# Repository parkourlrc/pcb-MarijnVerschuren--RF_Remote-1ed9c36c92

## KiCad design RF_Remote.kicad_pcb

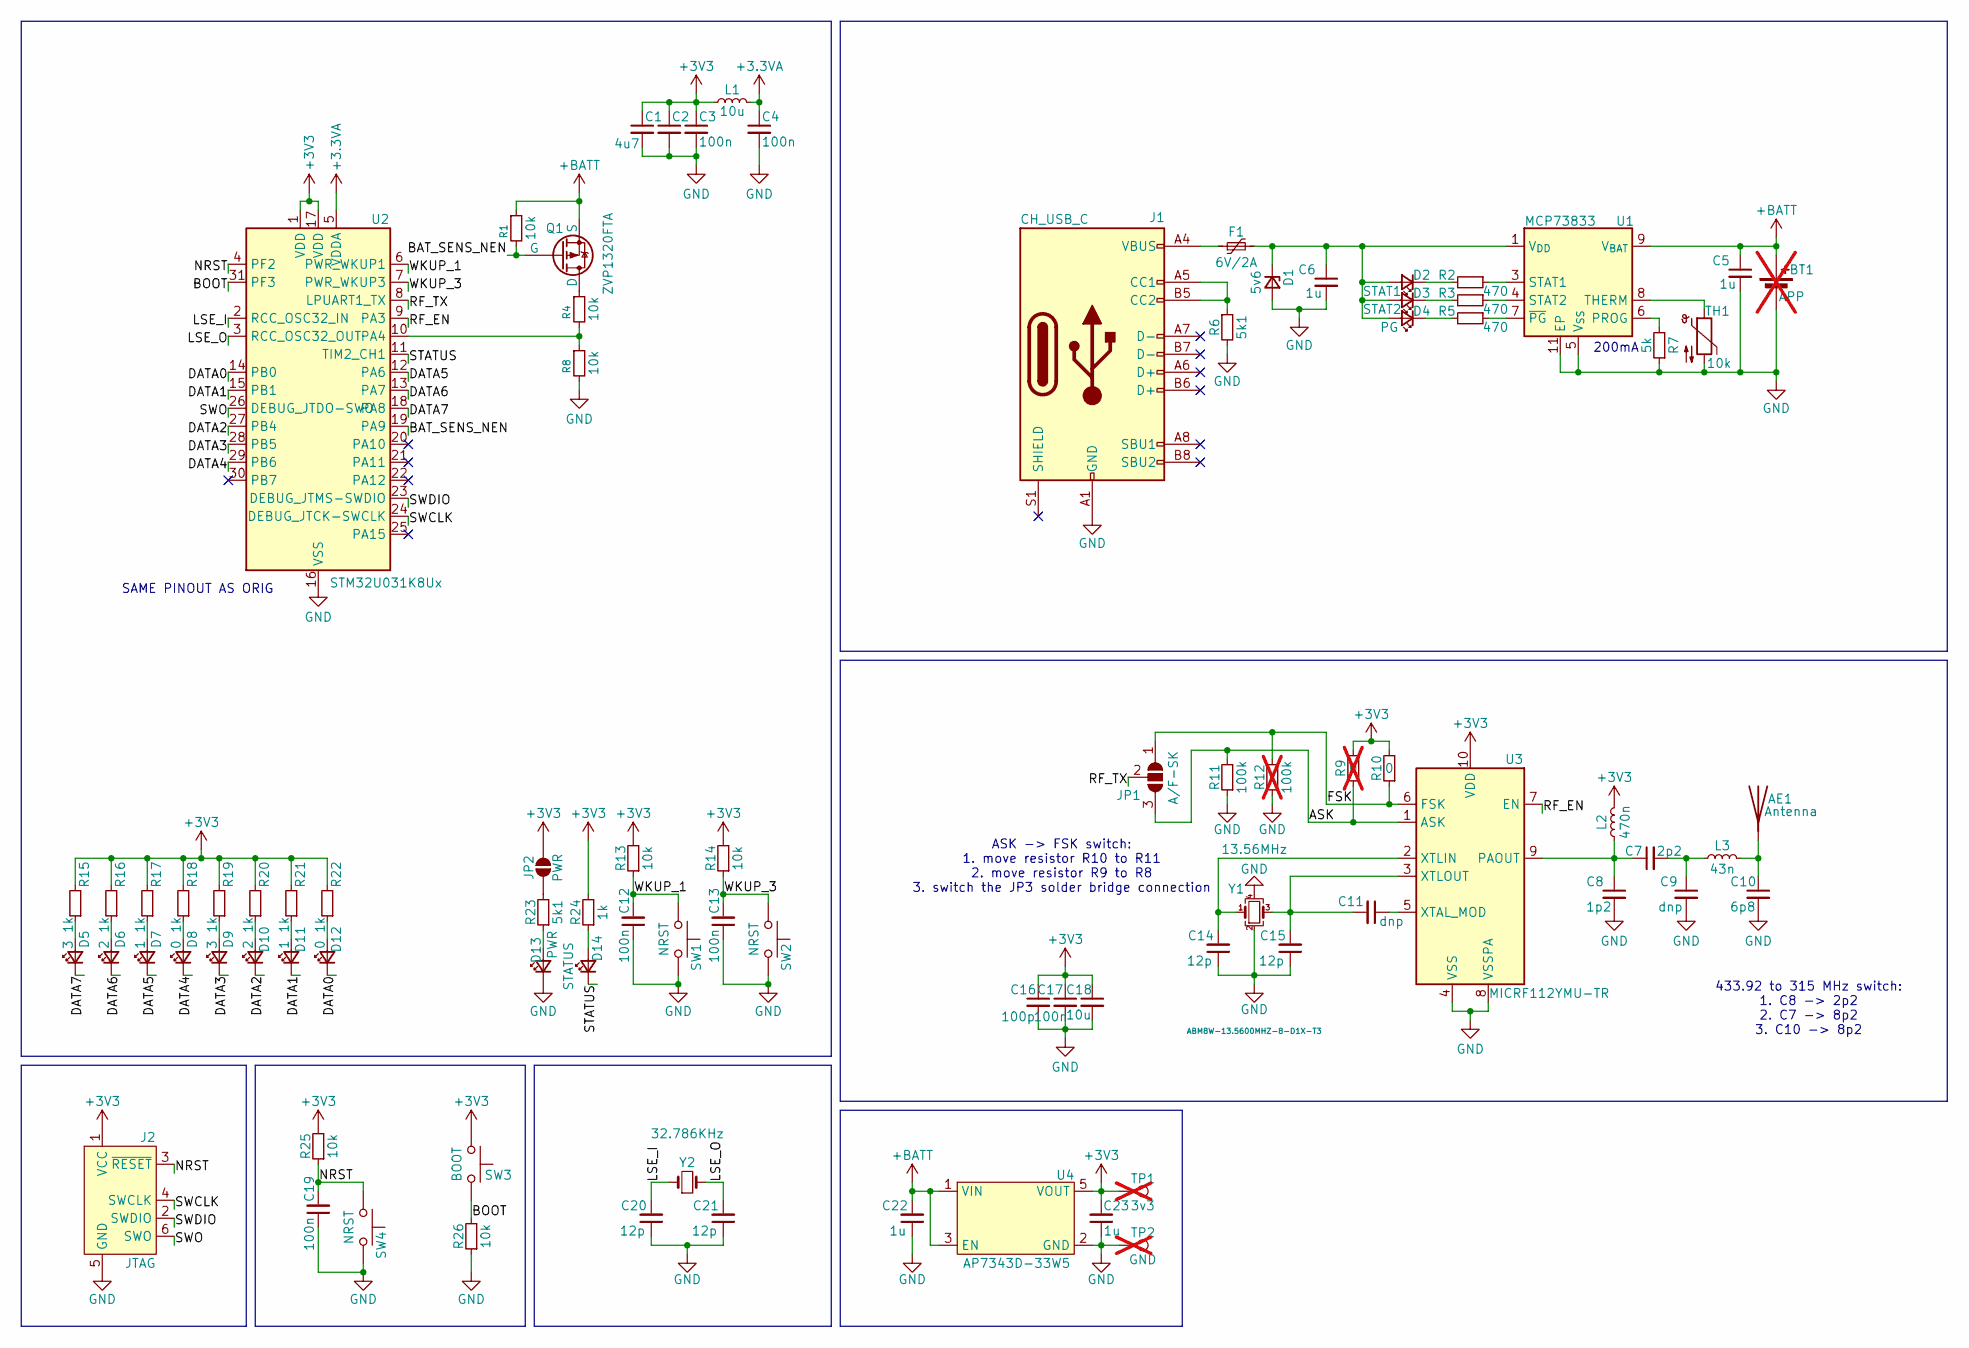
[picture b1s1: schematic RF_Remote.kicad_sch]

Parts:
AE1: Antenna; TestPoint_THTPad_D1.0mm_Drill0.5mm
BT1: APP; PinHeader_1x02_P2.54mm_Vertical; not fitted
C1: 4u7; C_0603_1608Metric
C2, C3, C4, C12, C13, C17, C19: 100n; C_0603_1608Metric
C5, C6: 1u; C_0603_1608Metric; mouser 963-MLAST168SB7105KT
C7: 2p2; C_0603_1608Metric
C8: 1p2; C_0603_1608Metric
C9, C11: dnp; C_0603_1608Metric
C10: 6p8; C_0603_1608Metric
C14, C15, C20, C21: 12p; C_0603_1608Metric
C16: 100p; C_0603_1608Metric
C18: 10u; C_0603_1608Metric
C22, C23: 1u; C_0603_1608Metric
D1: 5v6; D_SOD-123; mouser 78-BZT52C5V6-E3-08
D2: STAT1; LED_0603_1608Metric; mouser 710-150060AS75000
D3: STAT2; LED_0603_1608Metric; mouser 710-150060AS75000
D4: PG; LED_0603_1608Metric; mouser 710-150060RS75000
D5, D9: 3; LED_0603_1608Metric; mouser 710-150060AS75000
D6, D10: 2; LED_0603_1608Metric; mouser 710-150060AS75000
D7, D11: 1; LED_0603_1608Metric; mouser 710-150060AS75000
D8, D12: 0; LED_0603_1608Metric; mouser 710-150060AS75000
D13: PWR; LED_0603_1608Metric; mouser 710-150060AS75000
D14: STATUS; LED_0603_1608Metric; mouser 710-150060AS75000
F1: 6V/2A; Fuse_1206_3216Metric; mouser 504-PTS18126V260
J1: CH_USB_C; USB_C_Receptacle_HCTL_HC-TYPE-C-16P-01A
J2: JTAG; Tag-Connect_TC2030-IDC-FP_2x03_P1.27mm_Vertical
JP1: A/F-SK; SolderJumper-3_P2.0mm_Open_TrianglePad1.0x1.5mm_NumberLabels
JP2: PWR; SolderJumper-2_P1.3mm_Open_TrianglePad1.0x1.5mm
L1: 10u; L_0805_2012Metric
L2: 470n; L_0805_2012Metric
L3: 43n; L_0805_2012Metric
Q1: ZVP1320FTA; SOT-323; mouser 522-ZVP1320FTA
R1, R4, R8, R13, R14, R25, R26: 10k; R_0603_1608Metric
R2, R3, R5: 470; R_0603_1608Metric; LCSC C23186
R6: 5k1; R_0603_1608Metric; LCSC C23186
R7: 5k; R_0603_1608Metric; LCSC C23186
R9: 0; R_0603_1608Metric; not fitted
R10: 0; R_0603_1608Metric
R11: 100k; R_0603_1608Metric
R12: 100k; R_0603_1608Metric; not fitted
R15, R16, R17, R18, R19, R20, R21, R22, R24: 1k; R_0603_1608Metric
R23: 5k1; R_0603_1608Metric
SW1, SW2, SW4: NRST; SW_SPST_PTS810; LCSC C2681476
SW3: BOOT; SW_SPST_PTS810; LCSC C2681476
TH1: 10k; R_0603_1608Metric; mouser 667-ERT-J1VR103J
TP1: 3v3; TestPoint_Pad_D1.5mm; not fitted
TP2: GND; TestPoint_Pad_D1.5mm; not fitted
U1: MCP73833; DFN-10-1EP_3x3mm_P0.5mm_EP1.58x2.35mm; mouser 579-MCP73833T-AMI/MF
U2: STM32U031K8Ux; QFN-32-1EP_5x5mm_P0.5mm_EP3.45x3.45mm
U3: MICRF112YMU-TR; DFN-10-1EP_2.6x2.6mm_P0.5mm_EP1.3x2.2mm
U4: AP7343D-33W5; SOT-25
Y1: 13.56MHz; Crystal_SMD_3225-4Pin_3.2x2.5mm
Y2: 32.786KHz; Crystal_SMD_3215-2Pin_3.2x1.5mm

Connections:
+3.3VA: C4.1, L1.2, U2.5 (VDDA)
+3V3: C1.1, C2.1, C3.1, C16.1, C17.1, C18.1, C23.2, J2.1 (VCC), JP2.2 (B), L1.1, L2.2, R9.2, R10.2, R13.2, R14.2, R15.2, R16.2, R17.2, R18.2, R19.2, R20.2, R21.2, R22.2, R24.2, R25.2, SW3.1, TP1.1, U2.1 (VDD), U2.17 (VDD), U3.10 (VDD), U4.5 (VOUT)
+BATT: BT1.1 (+), C5.1, C22.2, Q1.3 (S), R1.1, U1.9 (V_{BAT}), U1.10 (V_{BAT}), U4.1 (VIN), U4.3 (EN)
/ASK: JP1.3 (B), R9.1, R11.2, U3.1 (ASK)
/BAT_SENS_NEN: Q1.2 (G), R1.2, U2.19 (PA9)
/BOOT: R26.2, SW3.2, U2.31 (PF3)
/DATA0: D12.1 (K), U2.14 (PB0)
/DATA1: D11.1 (K), U2.15 (PB1)
/DATA2: D10.1 (K), U2.27 (PB4)
/DATA3: D9.1 (K), U2.28 (PB5)
/DATA4: D8.1 (K), U2.29 (PB6)
/DATA5: D7.1 (K), U2.12 (PA6)
/DATA6: D6.1 (K), U2.13 (PA7)
/DATA7: D5.1 (K), U2.18 (PA8)
/FSK: JP1.1 (A), R10.1, R12.2, U3.6 (FSK)
/LSE_I: C20.2, U2.2 (RCC_OSC32_IN), Y2.1
/LSE_O: C21.2, U2.3 (RCC_OSC32_OUT), Y2.2
/NRST: C19.2, J2.3 (~RESET), R25.1, SW4.1, U2.4 (PF2)
/RF_EN: U2.9 (PA3), U3.7 (EN)
/RF_TX: JP1.2 (C), U2.8 (LPUART1_TX)
/STATUS: D14.1 (K), U2.11 (TIM2_CH1)
/SWCLK: J2.4 (SWCLK), U2.24 (DEBUG_JTCK-SWCLK)
/SWDIO: J2.2 (SWDIO), U2.23 (DEBUG_JTMS-SWDIO)
/SWO: J2.6 (SWO), U2.26 (DEBUG_JTDO-SWO)
/WKUP_1: C12.2, R13.1, SW1.1, U2.6 (PWR_WKUP1)
/WKUP_3: C13.2, R14.1, SW2.1, U2.7 (PWR_WKUP3)
GND: BT1.2 (-), C1.2, C2.2, C3.2, C4.2, C5.2, C6.2, C8.2, C9.2, C10.2, C12.1, C13.1, C14.1, C15.1, C16.2, C17.2, C18.2, C19.1, C20.1, C21.1, C22.1, C23.1, D1.2 (A), D13.1 (K), J1.A1 (GND), J1.A12 (GND), J1.B1 (GND), J1.B12 (GND), J2.5 (GND), R6.2, R7.1, R8.2, R11.1, R12.1, R26.1, SW1.2, SW2.2, SW4.2, TH1.2, TP2.1, U1.5 (V_{SS}), U1.11 (EP), U2.16 (VSS), U2.32 (VSS), U2.33 (VSS), U3.4 (VSS), U3.8 (VSSPA), U4.2 (GND), Y1.2, Y1.4
unnamed: AE1.1 (A), C10.1, L3.2
unnamed: C7.2, C9.1, L3.1
unnamed: C6.1, D1.1 (K), D2.2 (A), D3.2 (A), D4.2 (A), F1.2, U1.1 (V_{DD}), U1.2 (V_{DD})
unnamed: D2.1 (K), R2.2
unnamed: D3.1 (K), R3.2
unnamed: D4.1 (K), R5.2
unnamed: D5.2 (A), R15.1
unnamed: D6.2 (A), R16.1
unnamed: D7.2 (A), R17.1
unnamed: D8.2 (A), R18.1
unnamed: D9.2 (A), R19.1
unnamed: D10.2 (A), R20.1
unnamed: D11.2 (A), R21.1
unnamed: D12.2 (A), R22.1
unnamed: D13.2 (A), R23.1
unnamed: D14.2 (A), R24.1
unnamed: F1.1, J1.A4 (VBUS), J1.A9 (VBUS), J1.B4 (VBUS), J1.B9 (VBUS)
unnamed: J1.A5 (CC1), J1.B5 (CC2), R6.1
unnamed: JP2.1 (A), R23.2
unnamed: Q1.1 (D), R4.1
unnamed: R7.2, U1.6 (PROG)
unnamed: R2.1, U1.3 (STAT1)
unnamed: R3.1, U1.4 (STAT2)
unnamed: TH1.1, U1.8 (THERM)
unnamed: R5.1, U1.7 (~PG)
unnamed: R4.2, R8.1, U2.10 (PA4)
unnamed: C7.1, C8.1, L2.1, U3.9 (PAOUT)
unnamed: C11.1, U3.5 (XTAL_MOD)
unnamed: C14.2, U3.2 (XTLIN), Y1.1
unnamed: C11.2, C15.2, U3.3 (XTLOUT), Y1.3

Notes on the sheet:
200mA
ASK -> FSK switch: 1. move resistor R10 to R11 2. move resistor R9 to R8 3. switch the JP3 solder bridge connection
433.92 to 315 MHz switch: 1. C8 -> 2p2 2. C7 -> 8p2 3. C10 -> 8p2
SAME PINOUT AS ORIG

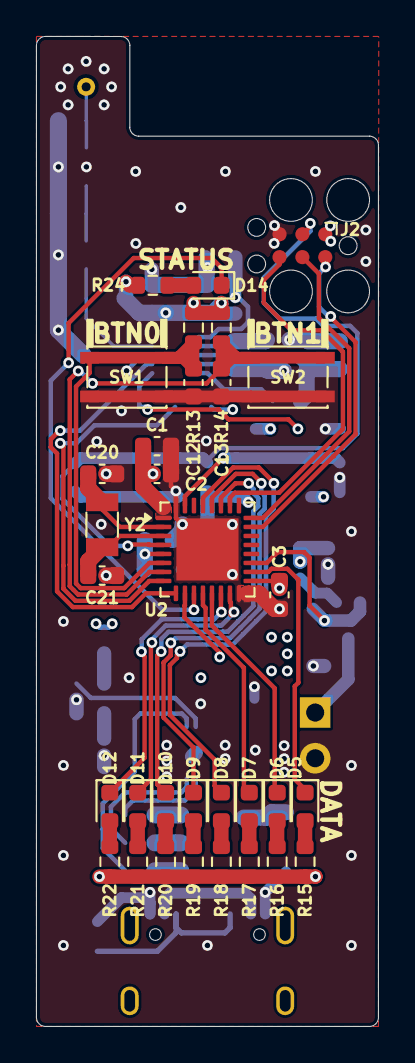
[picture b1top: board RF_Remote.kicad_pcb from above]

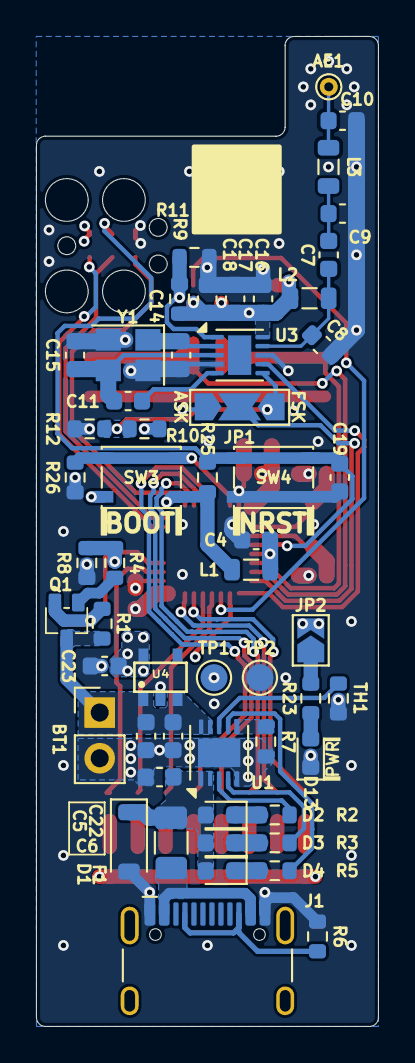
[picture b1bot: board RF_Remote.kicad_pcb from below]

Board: 4 copper layers, 19.0 x 55.0 mm, 87 parts (55 on the bottom side), 57 nets.

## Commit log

2025-08-14 Added JLCPCB QR code and added user info
2025-08-15 Fixed RF data pull up/down resistors
2025-08-20 Fixed power section
2026-02-22 Final changes
